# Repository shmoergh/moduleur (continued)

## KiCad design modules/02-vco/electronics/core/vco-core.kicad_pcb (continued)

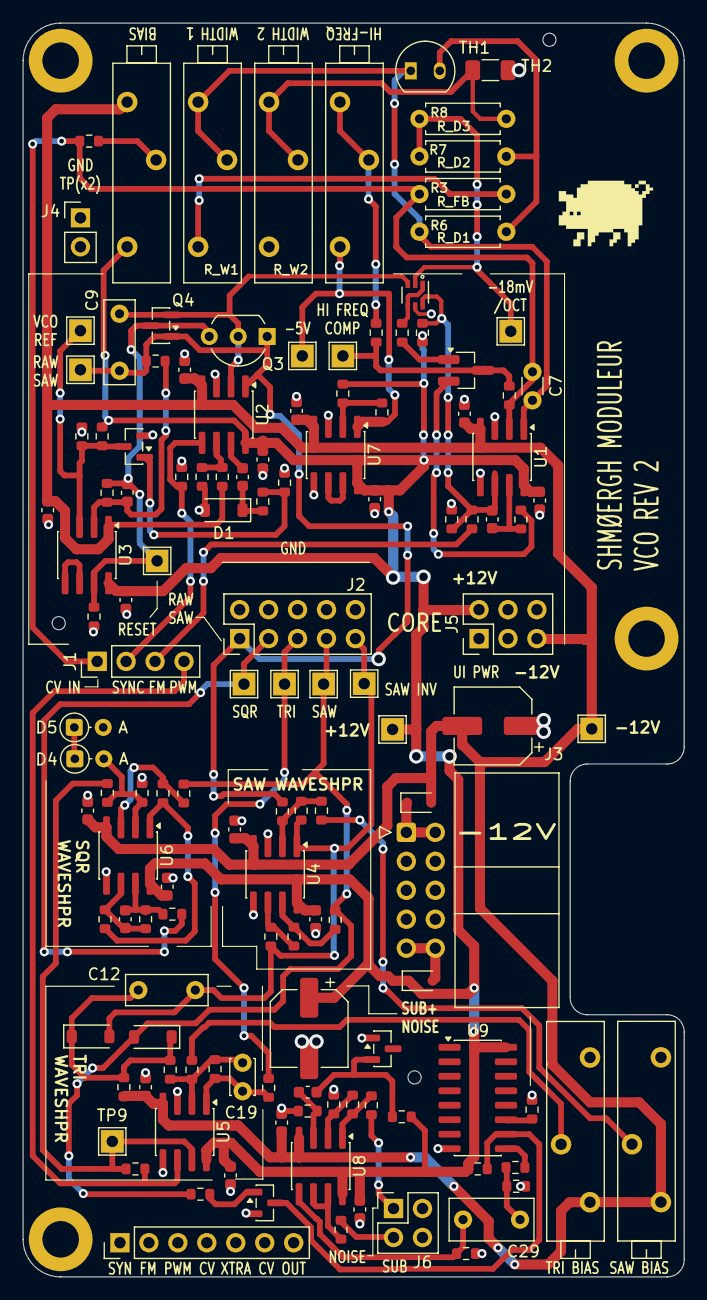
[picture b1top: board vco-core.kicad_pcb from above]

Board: 2 copper layers, 58.0 x 110.0 mm, 138 parts (0 on the bottom side), 67 nets.

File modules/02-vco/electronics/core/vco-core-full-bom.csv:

"Reference","Value","Qty","Exclude from BOM","Footprint","LCSC","Mouser Part no.","Part URL","Vendor","CHECKED"
"C1,C2,C3,C4,C5,C6,C13,C14,C15,C16,C17,C18,C21,C22,C26,C27","100n","16","","Capacitor_SMD:C_0603_1608Metric","C14663","","","JLCPCB","YES"
"C8","100p","1","","Capacitor_SMD:C_0603_1608Metric","C14858","","","JLCPCB","YES"
"C9","2.2nF (foil)","1","","Capacitor_THT:C_Rect_L7.2mm_W2.5mm_P5.00mm_FKS2_FKP2_MKS2_MKP2","","80-R82MC1220AA50J ","https://mou.sr/4eLPHe3","Mouser","YES"
"C10","22p","1","","Capacitor_SMD:C_0603_1608Metric","C1653","","","JLCPCB","YES"
"C11","47p","1","","Capacitor_SMD:C_0603_1608Metric","C1671","","","JLCPCB","YES"
"C20","33p","1","","Capacitor_SMD:C_0603_1608Metric","C1663","","","JLCPCB","YES"
"C23,C24","100u","2","","Capacitor_SMD:CP_Elec_6.3x7.7","C2836442","","","JLCPCB","YES"
"C28","1u","1","","Capacitor_SMD:C_0603_1608Metric","C15849","","","JLCPCB","YES"
"C29","470n","1","","Capacitor_THT:C_Rect_L7.2mm_W3.5mm_P5.00mm_FKS2_FKP2_MKS2_MKP2","","80-R82DC3470DQ60K","https://mou.sr/4lPhH2D","Mouser","YES"
"D1,D2,D3","1N4148","3","","Diode_SMD:D_SOD-123","C81598","","","JLCPCB","YES"
"D6,D7","1N5817","2","","Diode_SMD:D_SOD-323","C5190152","","","JLCPCB","YES"
"J1","Conn_01x04","1","","Connector_PinHeader_2.54mm:PinHeader_1x04_P2.54mm_Vertical","","200-HTSW10407TS","https://mou.sr/3UfnMcJ","Mouser","YES"
"J2","Conn_02x05_Odd_Even","1","","Connector_PinHeader_2.54mm:PinHeader_2x05_P2.54mm_Vertical","","200-TSW10507TD","https://mou.sr/40QhDaC","Mouser","YES"
"J3","Conn_02x05_Odd_Even","1","","Connector_IDC:IDC-Header_2x05_P2.54mm_Horizontal","","571-5103310-1","https://mou.sr/3GwYxj9","Mouser","YES"
"J4","Conn_01x02","1","","Connector_PinHeader_2.54mm:PinHeader_1x02_P2.54mm_Vertical","","200-HTSW10207TS","https://mou.sr/3IruU3e","Mouser","YES"
"J5","Conn_02x03_Odd_Even","1","","Connector_PinHeader_2.54mm:PinHeader_2x03_P2.54mm_Vertical","","200-TSW10307TD","https://mou.sr/4liCQlU","Mouser","YES"
"J6","Conn_02x02_Counter_Clockwise","1","","Connector_PinHeader_2.54mm:PinHeader_2x02_P2.54mm_Vertical","","200-HTSW10207TD","https://mou.sr/3TDBcz9","Mouser","YES"
"J8","Conn_01x07","1","","Connector_PinHeader_2.54mm:PinHeader_1x07_P2.54mm_Vertical","","474-PRT-09280","","Mouser",""
"Q1","BC847BS","1","","Package_TO_SOT_SMD:SOT-363_SC-70-6","C5380687","","","JLCPCB","YES"
"Q2","MMBT3906","1","","Package_TO_SOT_SMD:SOT-23_Handsoldering","C7420354","","","JLCPCB","YES"
"Q3","J111","1","","Package_TO_SOT_THT:TO-92_Inline_Wide","","512-J111","https://mou.sr/4f5W0HS","Mouser","YES"
"Q4","MMBFJ111","1","","Package_TO_SOT_SMD:SOT-23","C274688","","","JLCPCB","YES"
"Q5,Q7","MMBT5551","2","","Package_TO_SOT_SMD:SOT-23","C2145","","","JLCPCB","YES"
"Q6","BC847","1","","Package_TO_SOT_SMD:SOT-23","C8664","","","JLCPCB","YES"
"R1,R5,R15,R18,R21,R25,R27,R28,R29,R30,R37,R38,R40,R41,R43,R57","100k","16","","Resistor_SMD:R_0603_1608Metric","C25803","","","JLCPCB","YES"
"R2,R17","150k","2","","Resistor_SMD:R_0603_1608Metric","C22807","","","JLCPCB","YES"
"R3,R6,R7,R8","See t.comp. table","4","","Shmoergh_Custom_Footprints:R_Axial_DIN0207_L6.3mm_D2.5mm_P7.62mm_Horizontal","","","https://hu.mouser.com/ProductDetail/YAGEO/MFR50SFTE52-4R22?q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","",""
"R4,R10,R13","1M","3","","Resistor_SMD:R_0603_1608Metric","C22935","","","JLCPCB","YES"
"R9,R11","1.5k","2","","Resistor_SMD:R_0603_1608Metric","C22843","","","JLCPCB","YES"
"R12","510","1","","Resistor_SMD:R_0603_1608Metric","C23193","","","JLCPCB","YES"
"R14,R47","10k","2","","Resistor_SMD:R_0603_1608Metric","C25804","","","JLCPCB","YES"
"R16","22k","1","","Resistor_SMD:R_0603_1608Metric","C31850","","","JLCPCB","YES"
"R19","330k","1","","Resistor_SMD:R_0603_1608Metric","C23137","","","JLCPCB","YES"
"R20,R33","2.2k","2","","Resistor_SMD:R_0603_1608Metric","C4190","","","JLCPCB","YES"
"R22,R32,R45,R46","47k","4","","Resistor_SMD:R_0603_1608Metric","C25819","","","JLCPCB","YES"
"R23,R24","15k","2","","Resistor_SMD:R_0603_1608Metric","C22809","","","JLCPCB","YES"
"R26","27k","1","","Resistor_SMD:R_0603_1608Metric","C22967","","","JLCPCB","YES"
"R31,R34,R44,R56","220k","4","","Resistor_SMD:R_0603_1608Metric","C22961","","","JLCPCB","YES"
"R35","2.2M","1","","Resistor_SMD:R_0603_1608Metric","C22938","","","JLCPCB","YES"
"R36,R39","240k","2","","Resistor_SMD:R_0603_1608Metric","C4197","","","JLCPCB","YES"
"R42","680","1","","Resistor_SMD:R_0603_1608Metric","C23228","","","JLCPCB","YES"
"R48","56k","1","","Resistor_SMD:R_0603_1608Metric","C23206","","","JLCPCB","YES"
"R50,R52,R53,R54,R55","1k","5","","Resistor_SMD:R_0603_1608Metric","C21190","","","JLCPCB","YES"
"RV_SAW_BIAS1","10k (prec)","1","","Potentiometer_THT:Potentiometer_Bourns_3006P_Horizontal","","652-3006P-1-103-LF ","https://mou.sr/41xh2vW","Mouser","YES"
"RV_TRI_BIAS1,R_BIAS1","100k (prec)","2","","Potentiometer_THT:Potentiometer_Bourns_3006P_Horizontal","","652-3006P-1-104-LF","https://mou.sr/4ff5W1E","Mouser","YES"
"R_HIFREQ1","2k (prec)","1","","Potentiometer_THT:Potentiometer_Bourns_3006P_Horizontal","","652-3006P-1-202-LF","https://mou.sr/3ZK9AMt","Mouser","YES"
"R_WIDTH1,R_WIDTH2","See t.comp. table","2","","Potentiometer_THT:Potentiometer_Bourns_3006P_Horizontal","","652-3006P-1-501-LF,652-3006P-7-203-LF","https://mou.sr/3GyUiUc,https://mou.sr/41re1x3","Mouser",""
"TH1","See t.comp. table","1","","Package_TO_SOT_THT:TO-92-2","","594-2381-640-55103","https://mou.sr/4nM5nSy","Mouser","YES"
"TH2","PTS120602B100RP100","1","","Resistor_SMD:R_1206_3216Metric_Pad1.30x1.75mm_HandSolder","","594-PTS120601B100RP","https://hu.mouser.com/ProductDetail/594-PTS120601B100RP","Mouser","YES"
"U1,U2,U4,U5,U6,U7,U8","TL072","7","","Package_SO:SOIC-8_3.9x4.9mm_P1.27mm","C6961","","","JLCPCB","YES"
"U3","LM311","1","","Package_SO:SOIC-8_3.9x4.9mm_P1.27mm","C12597","","","JLCPCB","YES"
"U9","CD4040BM96","1","","Package_SO:SOIC-16_3.9x9.9mm_P1.27mm","C353974","","","JLCPCB","YES"
"C7","100p-1n","1","Excluded from BOM","Capacitor_THT:C_Disc_D3.0mm_W1.6mm_P2.50mm","","","","","YES"
"C12","10p-100p","1","Excluded from BOM","Capacitor_THT:C_Rect_L7.0mm_W2.5mm_P5.00mm","","","","","YES"
"C19","22p","1","Excluded from BOM","Capacitor_THT:C_Disc_D3.0mm_W2.0mm_P2.50mm","","","","","YES"
"D4,D5","5.1V","2","Excluded from BOM","Diode_THT:D_DO-34_SOD68_P2.54mm_Vertical_AnodeUp","","","","","YES"
"H1,H2,H3,H4","MountingHole","4","Excluded from BOM","MountingHole:MountingHole_3.2mm_M3_DIN965_Pad","","","","","YES"
"TP1","-18mV/V","1","Excluded from BOM","TestPoint:TestPoint_THTPad_2.0x2.0mm_Drill1.0mm","","","","","YES"
"TP2","HiFreq","1","Excluded from BOM","TestPoint:TestPoint_THTPad_2.0x2.0mm_Drill1.0mm","","","","","YES"
"TP3","RAW_SAW","1","Excluded from BOM","TestPoint:TestPoint_THTPad_2.0x2.0mm_Drill1.0mm","","","","","YES"
"TP4","VCOVREF","1","Excluded from BOM","TestPoint:TestPoint_THTPad_2.0x2.0mm_Drill1.0mm","","","","","YES"
"TP5","Reset OUT","1","Excluded from BOM","TestPoint:TestPoint_THTPad_2.0x2.0mm_Drill1.0mm","","","","","YES"
"TP6","SAWInv","1","Excluded from BOM","TestPoint:TestPoint_THTPad_2.0x2.0mm_Drill1.0mm","","","","","YES"
"TP7","SAW","1","Excluded from BOM","TestPoint:TestPoint_THTPad_2.0x2.0mm_Drill1.0mm","","","","","YES"
"TP8","TRI","1","Excluded from BOM","TestPoint:TestPoint_THTPad_2.0x2.0mm_Drill1.0mm","","","","","YES"
"TP9","PW","1","Excluded from BOM","TestPoint:TestPoint_THTPad_2.0x2.0mm_Drill1.0mm","","","","","YES"
"TP10","SQR","1","Excluded from BOM","TestPoint:TestPoint_THTPad_2.0x2.0mm_Drill1.0mm","","","","","YES"
"TP11","-5V","1","Excluded from BOM","TestPoint:TestPoint_THTPad_2.0x2.0mm_Drill1.0mm","","","","","YES"
"TP12","12V","1","Excluded from BOM","TestPoint:TestPoint_THTPad_2.0x2.0mm_Drill1.0mm","","","","","YES"
"TP13","-12V","1","Excluded from BOM","TestPoint:TestPoint_THTPad_2.0x2.0mm_Drill1.0mm","","","","","YES"

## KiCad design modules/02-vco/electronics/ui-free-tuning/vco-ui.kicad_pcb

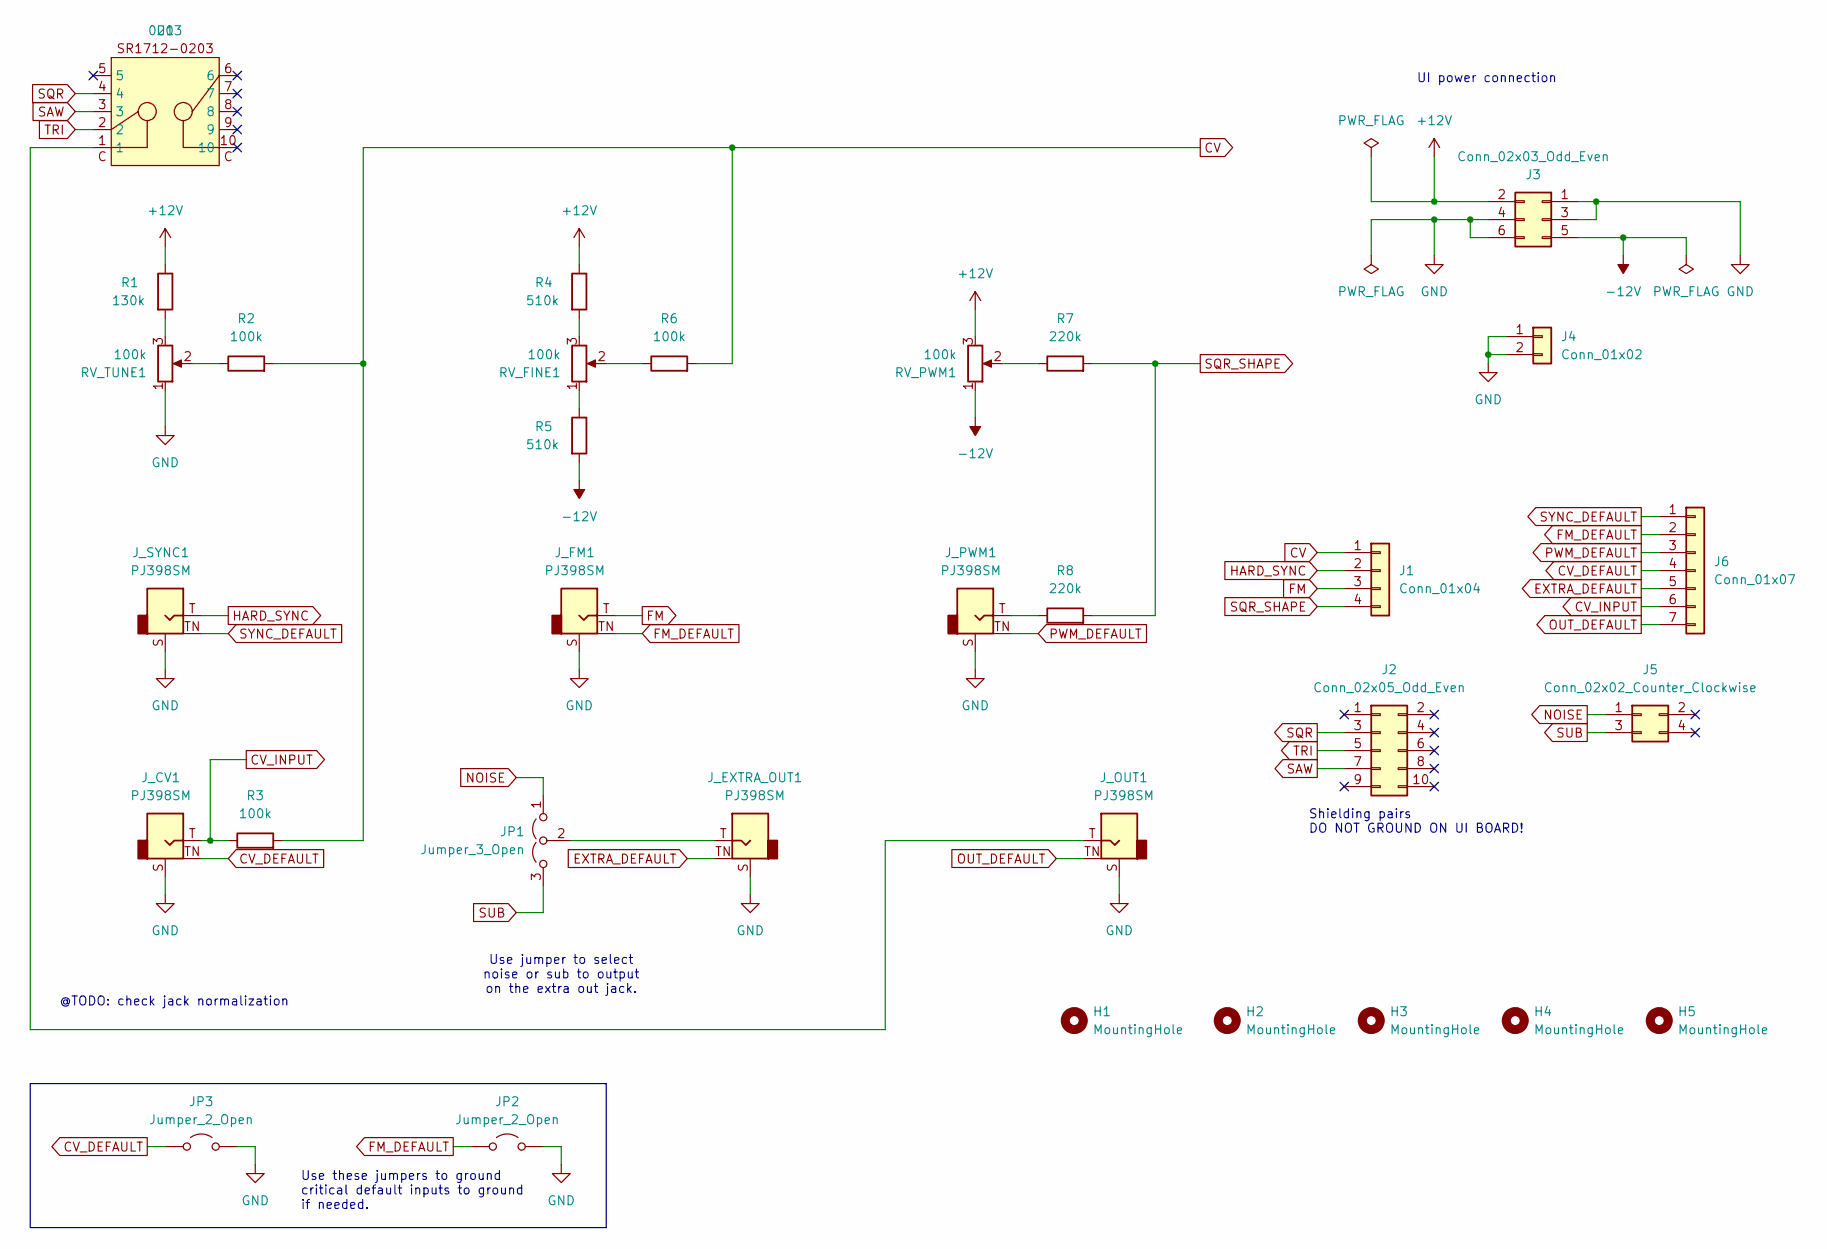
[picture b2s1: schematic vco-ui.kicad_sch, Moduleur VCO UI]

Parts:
H1, H2, H3, H4, H5: MountingHole; MountingHole_3.2mm_M3_DIN965_Pad
J1: Conn_01x04; PinSocket_1x04_P2.54mm_Vertical; Part no. 200-SSW10401TMS
J2: Conn_02x05_Odd_Even; PinSocket_2x05_P2.54mm_Vertical; Part no. 200-SSW10501TD
J3: Conn_02x03_Odd_Even; PinSocket_2x03_P2.54mm_Vertical; Part no. 200-SSW10301TD
J4: Conn_01x02; PinSocket_1x02_P2.54mm_Vertical; Part no. 200-SSW10201TS
J5: Conn_02x02_Counter_Clockwise; PinSocket_2x02_P2.54mm_Vertical; Part no. 200-SSW10206TD
J6: Conn_01x07; PinSocket_1x07_P2.54mm_Vertical; Part no. 200-SSW10601TS
JP1: Jumper_3_Open; PinHeader_1x03_P2.54mm_Horizontal; Part no. 200-HTSW10308TSRA
JP2, JP3: Jumper_2_Open; PinHeader_1x02_P2.54mm_Horizontal; Part no. 200-HTSW10208TSRA
J_CV1: PJ398SM; Jack_3.5mm_QingPu_WQP-PJ398SM_Vertical_CircularHoles; Part no. PJ398SM
J_EXTRA_OUT1: PJ398SM; Jack_3.5mm_QingPu_WQP-PJ398SM_Vertical_CircularHoles; Part no. PJ398SM
J_FM1: PJ398SM; Jack_3.5mm_QingPu_WQP-PJ398SM_Vertical_CircularHoles; Part no. PJ398SM
J_OUT1: PJ398SM; Jack_3.5mm_QingPu_WQP-PJ398SM_Vertical_CircularHoles; Part no. PJ398SM
J_PWM1: PJ398SM; Jack_3.5mm_QingPu_WQP-PJ398SM_Vertical_CircularHoles; Part no. PJ398SM
J_SYNC1: PJ398SM; Jack_3.5mm_QingPu_WQP-PJ398SM_Vertical_CircularHoles; Part no. PJ398SM
R1: 130k; R_Axial_DIN0207_L6.3mm_D2.5mm_P7.62mm_Horizontal; Part no. 603-MFR-25FBF52-130K
R2, R3, R6: 100k; R_Axial_DIN0207_L6.3mm_D2.5mm_P7.62mm_Horizontal; Part no. 603-MFR-25FRF52100K
R4, R5: 510k; R_Axial_DIN0207_L6.3mm_D2.5mm_P7.62mm_Horizontal; Part no. 603-MFR-25FBF52-510K
R7, R8: 220k; R_Axial_DIN0207_L6.3mm_D2.5mm_P7.62mm_Horizontal; Part no. 603-MFR-25FRF52-220K
RV_FINE1: 100k; Potentiometer_Bourns_Single-PTV09A; Part no. 652-PTV09A4025UB104
RV_PWM1: 100k; Potentiometer_Bourns_Single-PTV09A; Part no. 652-PTV09A4025UB104
RV_TUNE1: 100k; Potentiometer_Bourns_Single-PTV09A; Part no. 652-PTV09A4025UB104
U1: 0203; SR1712-0203; Part no. 105-SR1712F-23NS

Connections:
+12V: J3.2, R1.1, R4.1, RV_PWM1.3
-12V: J3.5, R5.2, RV_PWM1.1
CV: J1.1, R2.2, R3.2, R6.2
CV_DEFAULT: J6.4, JP3.1 (A), J_CV1.TN
CV_INPUT: J6.6, J_CV1.T, R3.1
EXTRA_DEFAULT: J6.5, J_EXTRA_OUT1.TN
FM: J1.3, J_FM1.T
FM_DEFAULT: J6.2, JP2.1 (A), J_FM1.TN
GND: J3.1, J3.3, J3.4, J3.6, J4.1, J4.2, JP2.2 (B), JP3.2 (B), J_CV1.S, J_EXTRA_OUT1.S, J_FM1.S, J_OUT1.S, J_PWM1.S, J_SYNC1.S, RV_TUNE1.1
HARD_SYNC: J1.2, J_SYNC1.T
NOISE: J5.1, JP1.1 (A)
unnamed: JP1.2 (C), J_EXTRA_OUT1.T
unnamed: J_OUT1.T, U1.1
unnamed: J_PWM1.T, R8.1
unnamed: R1.2, RV_TUNE1.3
unnamed: R2.1, RV_TUNE1.2
unnamed: R4.2, RV_FINE1.3
unnamed: R5.1, RV_FINE1.1
unnamed: R6.1, RV_FINE1.2
unnamed: R7.1, RV_PWM1.2
OUT_DEFAULT: J6.7, J_OUT1.TN
PWM_DEFAULT: J6.3, J_PWM1.TN
SAW: J2.7, U1.3
SQR: J2.3, U1.4
SQR_SHAPE: J1.4, R7.2, R8.2
SUB: J5.3, JP1.3 (B)
SYNC_DEFAULT: J6.1, J_SYNC1.TN
TRI: J2.5, U1.2

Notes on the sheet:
@TODO: check jack normalization
Use these jumpers to ground critical default inputs to ground if needed.
UI power connection
Use jumper to select noise or sub to output on the extra out jack.
Shielding pairs DO NOT GROUND ON UI BOARD!

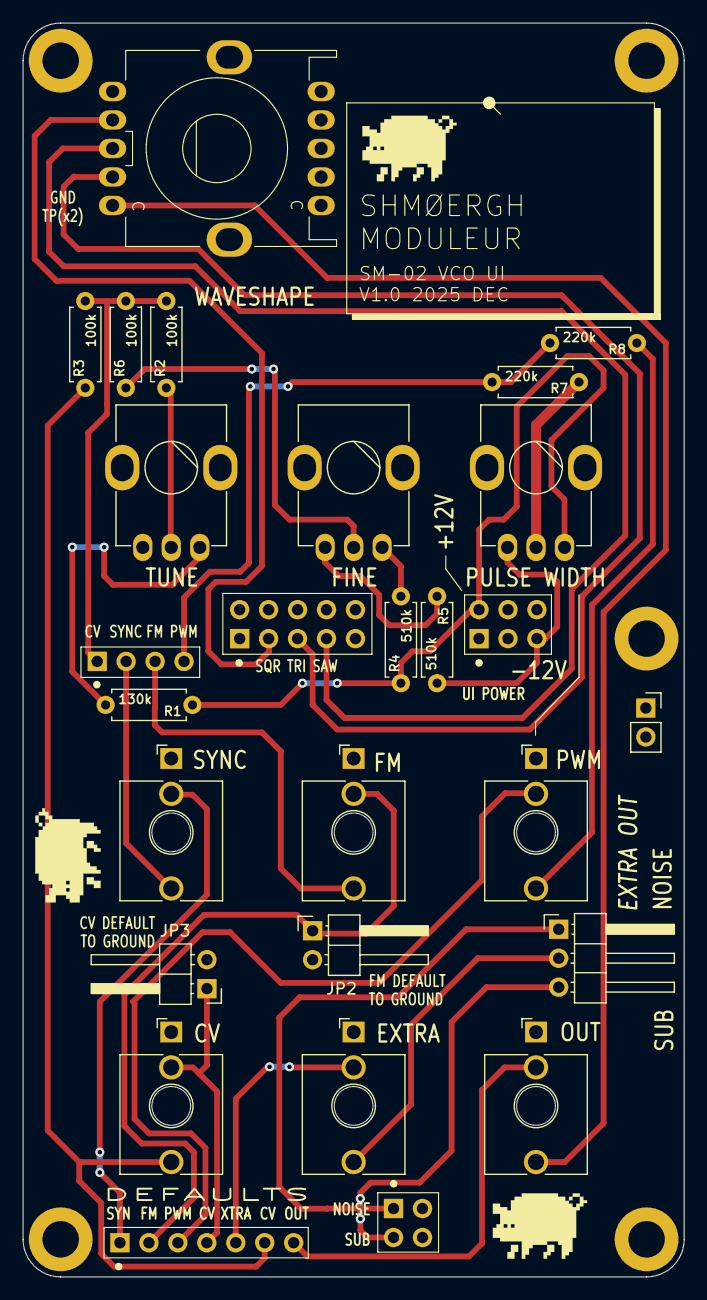
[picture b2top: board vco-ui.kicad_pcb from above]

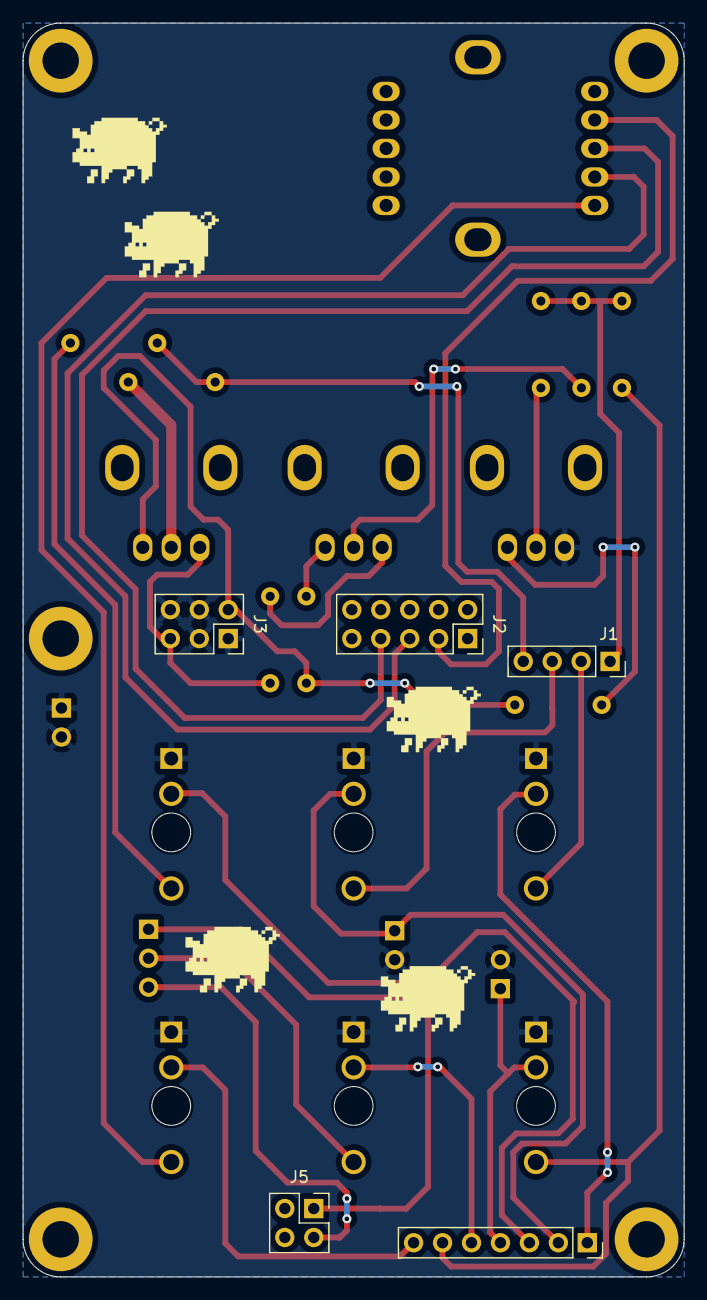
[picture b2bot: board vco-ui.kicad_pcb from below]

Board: 2 copper layers, 58.0 x 110.0 mm, 32 parts (5 on the bottom side), 28 nets.

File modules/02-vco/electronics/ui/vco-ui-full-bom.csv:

"Reference","Qty","Value","DNP","Exclude from BOM","Exclude from Board","Footprint","Datasheet","Part no.","Part URL","Vendor","Note"
"J1","1","Conn_01x04","","","","Connector_PinSocket_2.54mm:PinSocket_1x04_P2.54mm_Vertical","~","200-SSW10401TMS","https://mou.sr/4kxE3Vr","Mouser",""
"J2","1","Conn_02x05_Odd_Even","","","","Connector_PinSocket_2.54mm:PinSocket_2x05_P2.54mm_Vertical","~","200-SSW10501TD","https://mou.sr/4lVCZM9","Mouser",""
"J3","1","Conn_02x03_Odd_Even","","","","Connector_PinSocket_2.54mm:PinSocket_2x03_P2.54mm_Vertical","~","200-SSW10301TD","https://mou.sr/3GIDVEr","Mouser",""
"J4","1","Conn_01x02","","","","Connector_PinSocket_2.54mm:PinSocket_1x02_P2.54mm_Vertical","~","200-SSW10201TS","https://mou.sr/4lBvdHe","Mouser",""
"J5","1","Conn_02x02_Counter_Clockwise","","","","Connector_PinSocket_2.54mm:PinSocket_2x02_P2.54mm_Vertical","~","200-SSW10206TD","https://mou.sr/4eSbYqI","Mouser",""
"J6","1","Conn_01x07","","","","Connector_PinSocket_2.54mm:PinSocket_1x07_P2.54mm_Vertical","~","200-SSW10601TS","https://mou.sr/4lnf48h","Mouser",""
"JP1","1","Jumper_3_Open","","","","Connector_PinHeader_2.54mm:PinHeader_1x03_P2.54mm_Horizontal","~","200-HTSW10308TSRA","https://mou.sr/451l2py","Mouser",""
"JP2,JP3","2","Jumper_2_Open","","","","Connector_PinHeader_2.54mm:PinHeader_1x02_P2.54mm_Horizontal","~","200-HTSW10208TSRA","https://mou.sr/4nM6IZz","Mouser",""
"J_CV1,J_EXTRA_OUT1,J_FM1,J_OUT1,J_PWM1,J_SYNC1","6","PJ398SM","","","","Shmoergh_Custom_Footprints:Jack_3.5mm_QingPu_WQP-PJ398SM_Vertical_CircularHoles","~","PJ398SM","https://www.thonk.co.uk/shop/thonkiconn/","Thonk",""
"R1","1","130k","","","","Shmoergh_Custom_Footprints:R_Axial_DIN0207_L6.3mm_D2.5mm_P7.62mm_Horizontal","~","603-MFR-25FBF52-130K ","https://mou.sr/3XNtowV","Mouser",""
"R2,R3,R6","3","100k","","","","Shmoergh_Custom_Footprints:R_Axial_DIN0207_L6.3mm_D2.5mm_P7.62mm_Horizontal","~","603-MFR-25FRF52100K","https://mou.sr/4hEwI4G","Mouser",""
"R4,R5","2","510k","","","","Shmoergh_Custom_Footprints:R_Axial_DIN0207_L6.3mm_D2.5mm_P7.62mm_Horizontal","~","603-MFR-25FBF52-510K ","https://mou.sr/44Vd3Kk","Mouser",""
"R7,R8","2","220k","","","","Shmoergh_Custom_Footprints:R_Axial_DIN0207_L6.3mm_D2.5mm_P7.62mm_Horizontal","~","603-MFR-25FRF52-220K","https://mou.sr/46cEvF7","Mouser",""
"RV_FINE1,RV_PWM1,RV_TUNE1","3","100k","","","","Shmoergh_Custom_Footprints:Potentiometer_Bourns_Single-PTV09A","~","652-PTV09A4025UB104","https://mou.sr/41lYe2k","Mouser","Knurled Shaft"
"U1","1","0203","","","","Shmoergh_Custom_Footprints:SR1712-0203","https://hu.mouser.com/datasheet/2/13/SR1712F-1815245.pdf","105-SR1712F-23NS","https://mou.sr/3U6bGTk","Mouser",""

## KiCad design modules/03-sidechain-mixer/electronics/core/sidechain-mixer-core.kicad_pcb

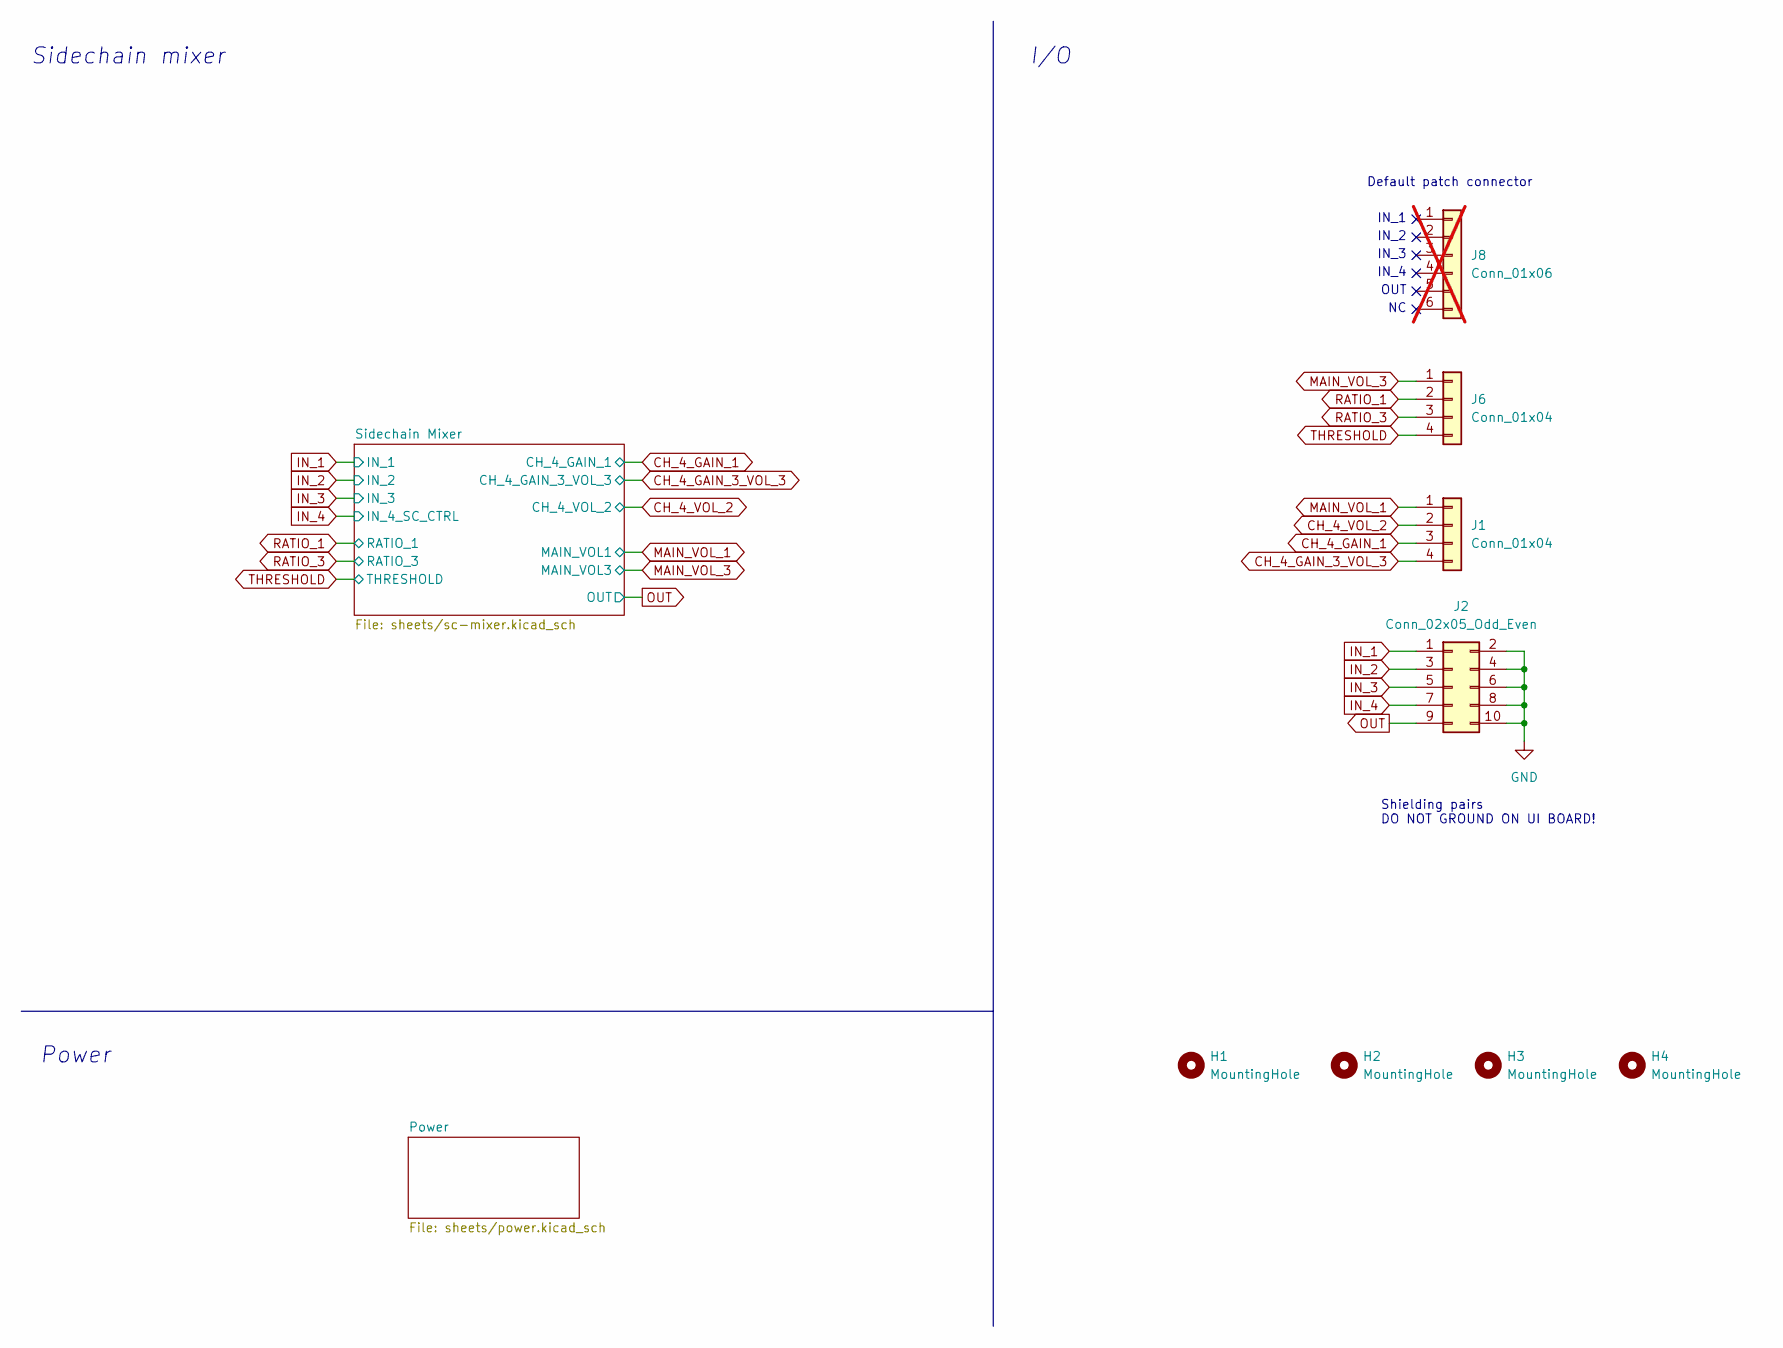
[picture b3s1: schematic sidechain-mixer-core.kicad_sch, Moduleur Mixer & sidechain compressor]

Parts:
H1, H2, H3, H4: MountingHole; MountingHole_3.2mm_M3_DIN965_Pad
J1, J6: Conn_01x04; PinHeader_1x04_P2.54mm_Vertical; Mouser Part no. 200-HTSW10407TS
J2: Conn_02x05_Odd_Even; PinHeader_2x05_P2.54mm_Vertical; Mouser Part no. 200-HTSW10507TD
J8: Conn_01x06; PinHeader_1x06_P2.54mm_Vertical; Mouser Part no. 200-HTSW10607TS; not fitted

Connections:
CH_4_GAIN_1: J1.3; also elsewhere on the board
CH_4_GAIN_3_VOL_3: J1.4; also elsewhere on the board
CH_4_VOL_2: J1.2; also elsewhere on the board
IN_1: J2.1; also elsewhere on the board
IN_2: J2.3; also elsewhere on the board
IN_3: J2.5; also elsewhere on the board
IN_4: J2.7; also elsewhere on the board
MAIN_VOL_1: J1.1; also elsewhere on the board
MAIN_VOL_3: J6.1; also elsewhere on the board
OUT: J2.9; also elsewhere on the board
RATIO_1: J6.2; also elsewhere on the board
RATIO_3: J6.3; also elsewhere on the board
THRESHOLD: J6.4; also elsewhere on the board

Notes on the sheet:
Power
IN_3
Default patch connector
IN_1
Shielding pairs DO NOT GROUND ON UI BOARD!
OUT
Sidechain mixer
IN_2
I/O
IN_4

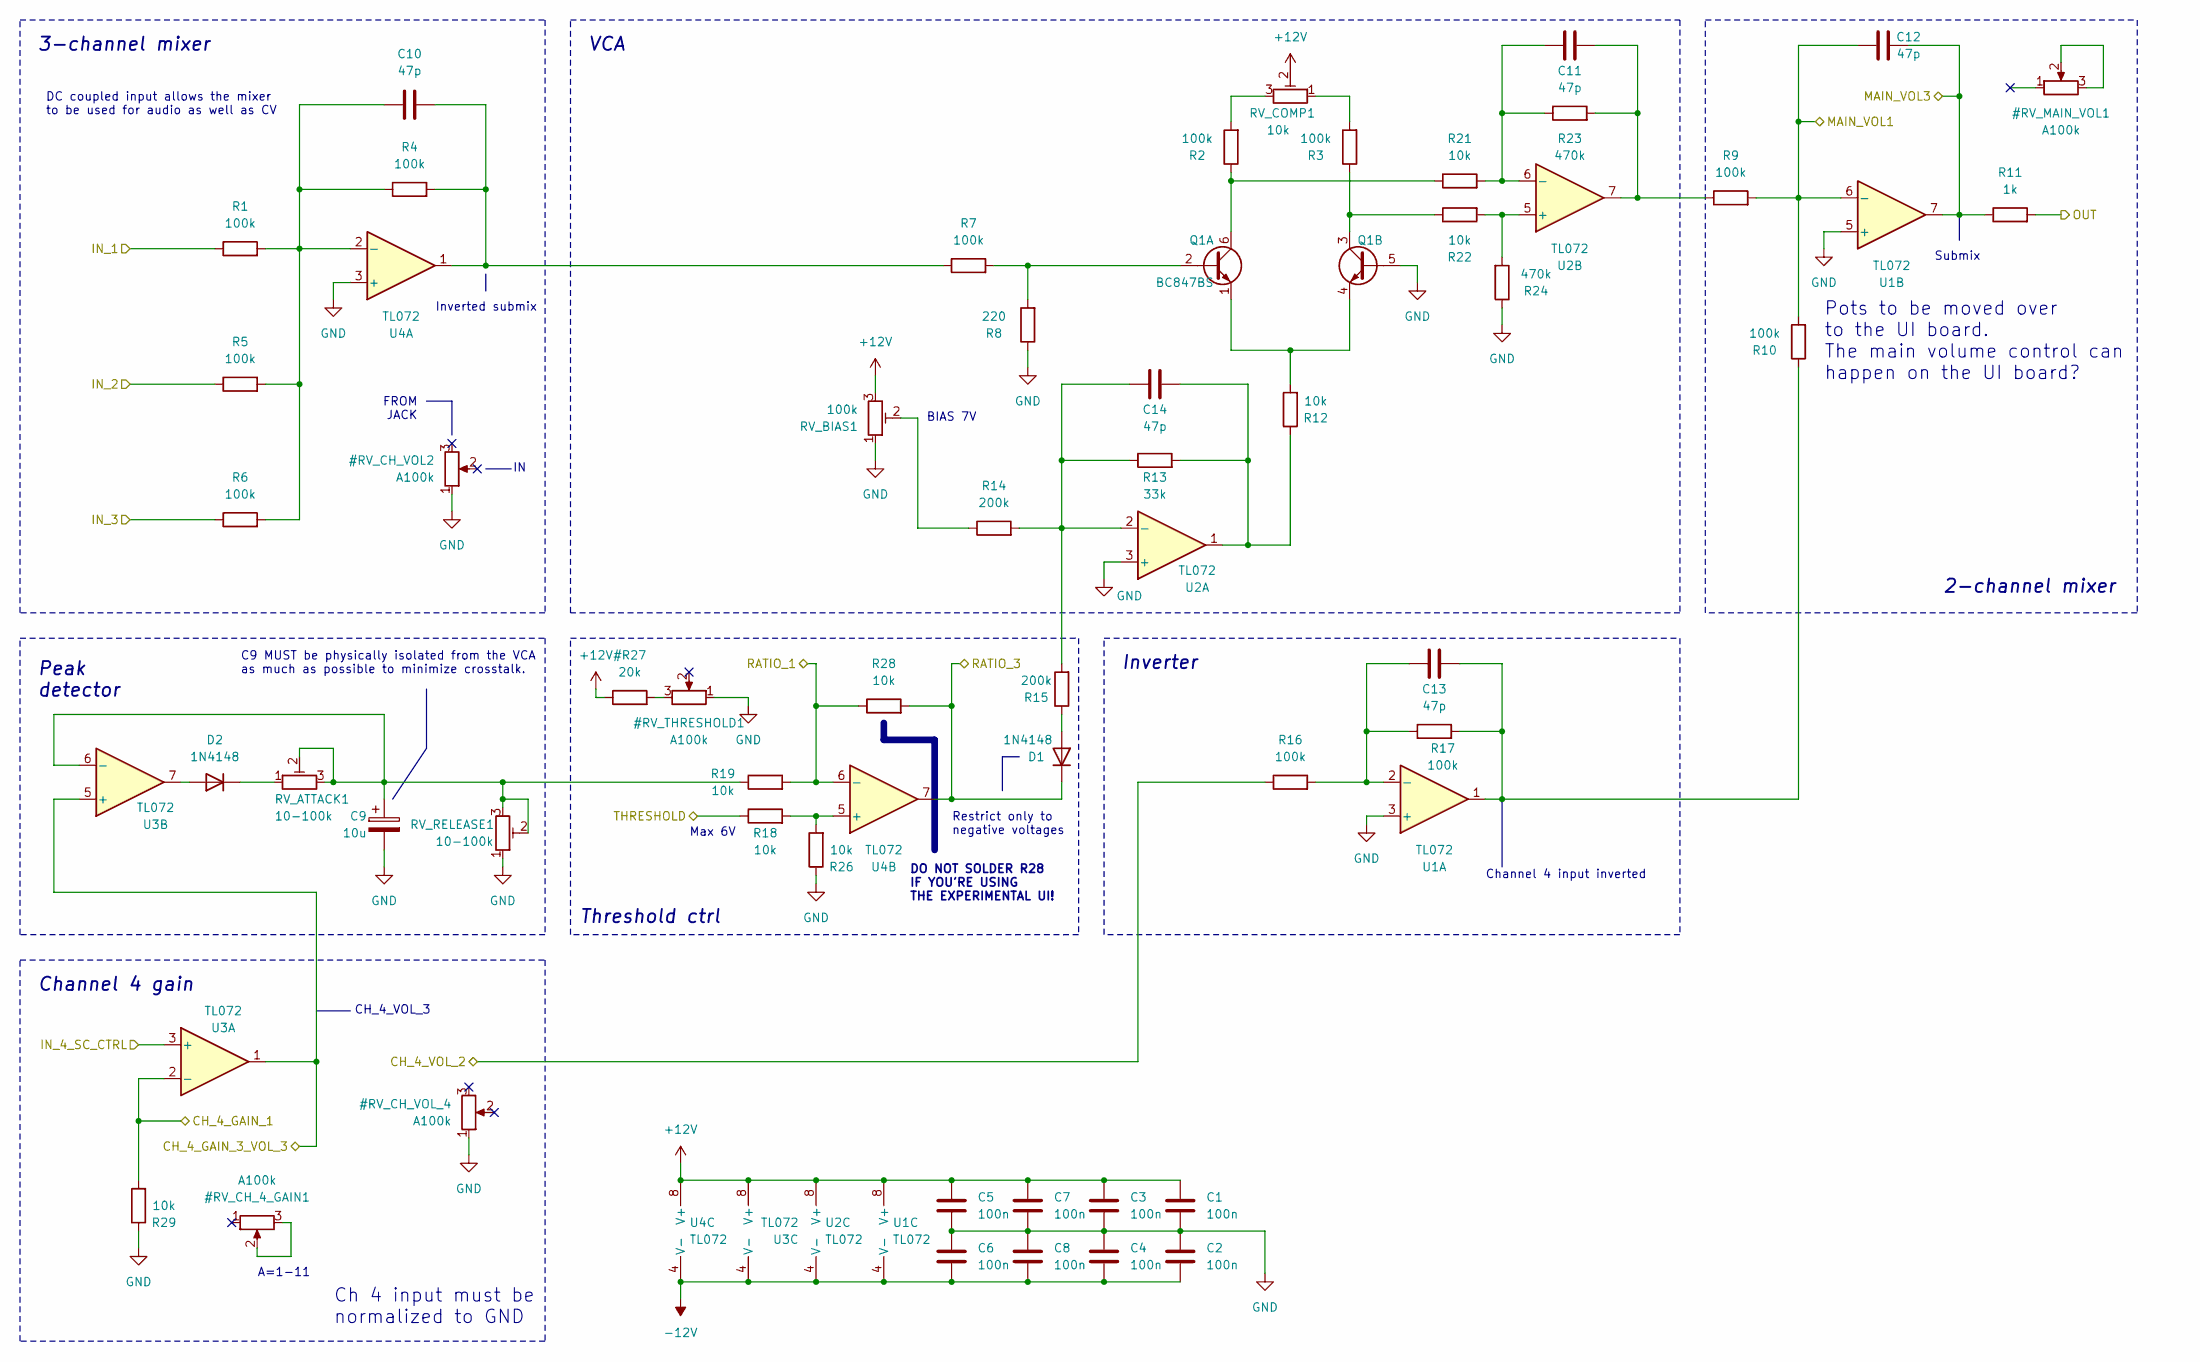
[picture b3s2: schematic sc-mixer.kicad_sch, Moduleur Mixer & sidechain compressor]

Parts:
C1, C2, C3, C4, C5, C6, C7, C8: 100n; C_0603_1608Metric; LCSC C14663
C9: 10u; CP_Elec_5x5.4; LCSC C30110
C10, C11, C12, C13, C14: 47p; C_0603_1608Metric_Pad1.08x0.95mm_HandSolder; LCSC C1671
D1, D2: 1N4148; D_SOD-123; LCSC C81598
Q1: BC847BS; SOT-363_SC-70-6; LCSC C5380687
R1, R2, R3, R4, R5, R6, R7, R9, R10, R16, R17: 100k; R_0603_1608Metric; LCSC C25803
R8: 220; R_0603_1608Metric; LCSC C22962
R11: 1k; R_0603_1608Metric; LCSC C21190
R12, R21, R22: 10k; R_0603_1608Metric; LCSC C25804
R13: 33k; R_0603_1608Metric; LCSC C4216
R14, R15: 200k; R_0603_1608Metric; LCSC C25811
R18, R19, R26, R28, R29: 10k; R_Axial_DIN0207_L6.3mm_D2.5mm_P7.62mm_Horizontal; Mouser Part no. 603-MFR-25FRF5210K
R23, R24: 470k; R_0603_1608Metric; LCSC C23178
RV_ATTACK1: 10-100k; Potentiometer_ACP_CA6-H2,5_Horizontal; Mouser Part no. 774-06TR4AA103CP
RV_BIAS1: 100k; Potentiometer_ACP_CA6-H2,5_Horizontal; Mouser Part no. 774-06TR4AA104CP
RV_COMP1: 10k; Potentiometer_ACP_CA6-H2,5_Horizontal; Mouser Part no. 774-06TR4AA103CP
RV_RELEASE1: 10-100k; Potentiometer_ACP_CA6-H2,5_Horizontal; Mouser Part no. 774-06TR4AA103CP
U1, U2, U3, U4: TL072; SOIC-8_3.9x4.9mm_P1.27mm; LCSC C6961

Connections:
-12V: C2.2, C4.2, C6.2, C8.2, U1.4 (V-), U2.4 (V-), U3.4 (V-), U4.4 (V-); also elsewhere on the board
CH_4_GAIN_1: R29.2, U3.2 (-); also elsewhere on the board
CH_4_GAIN_3_VOL_3: U3.1, U3.5 (+); also elsewhere on the board
CH_4_VOL_2: R16.1; also elsewhere on the board
IN_1: R1.1; also elsewhere on the board
IN_2: R5.1; also elsewhere on the board
IN_3: R6.1; also elsewhere on the board
IN_4: U3.3 (+); also elsewhere on the board
MAIN_VOL_1: C12.1, R9.2, R10.2, U1.6 (-); also elsewhere on the board
MAIN_VOL_3: C12.2, R11.1, U1.7; also elsewhere on the board
unnamed: C10.2, R4.2, R7.1, U4.1
unnamed: C11.2, R9.1, R23.2, U2.7
unnamed: C13.2, R10.1, R17.2, U1.1
unnamed: C14.2, R12.1, R13.2, U2.1
unnamed: D1.2 (A), R15.1
unnamed: D2.2 (A), U3.7
unnamed: D2.1 (K), RV_ATTACK1.1
unnamed: Q1.2 (B1), R7.2, R8.2
unnamed: Q1.6 (C1), R2.1, R21.1
unnamed: Q1.1 (E1), Q1.4 (E2), R12.2
unnamed: Q1.3 (C2), R3.1, R22.1
unnamed: R2.2, RV_COMP1.3
unnamed: R3.2, RV_COMP1.1
unnamed: R14.1, RV_BIAS1.2
unnamed: C13.1, R16.2, R17.1, U1.2 (-)
unnamed: C14.1, R13.1, R14.2, R15.2, U2.2 (-)
unnamed: R22.2, R24.2, U2.5 (+)
unnamed: C11.1, R21.2, R23.1, U2.6 (-)
unnamed: C9.1, R19.1, RV_ATTACK1.2, RV_ATTACK1.3, RV_RELEASE1.2, RV_RELEASE1.3, U3.6 (-)
unnamed: C10.1, R1.2, R4.1, R5.2, R6.2, U4.2 (-)
unnamed: R18.2, R26.2, U4.5 (+)
OUT: R11.2; also elsewhere on the board
RATIO_1: R19.2, R28.1, U4.6 (-); also elsewhere on the board
RATIO_3: D1.1 (K), R28.2, U4.7; also elsewhere on the board
THRESHOLD: R18.1; also elsewhere on the board

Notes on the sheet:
2-channel mixer
Channel 4 gain
FROM JACK
A=1-11
Pots to be moved over to the UI board. The main volume control can happen on the UI board?
DO NOT SOLDER R28 IF YOU'RE USING THE EXPERIMENTAL UI!
Inverter
Submix
VCA
BIAS 7V
Channel 4 input inverted
Max 6V
Ch 4 input must be normalized to GND
3-channel mixer
Restrict only to negative voltages
DC coupled input allows the mixer to be used for audio as well as CV
C9 MUST be physically isolated from the VCA as much as possible to minimize crosstalk.
CH_4_VOL_3
Peak detector
Threshold ctrl
Inverted submix

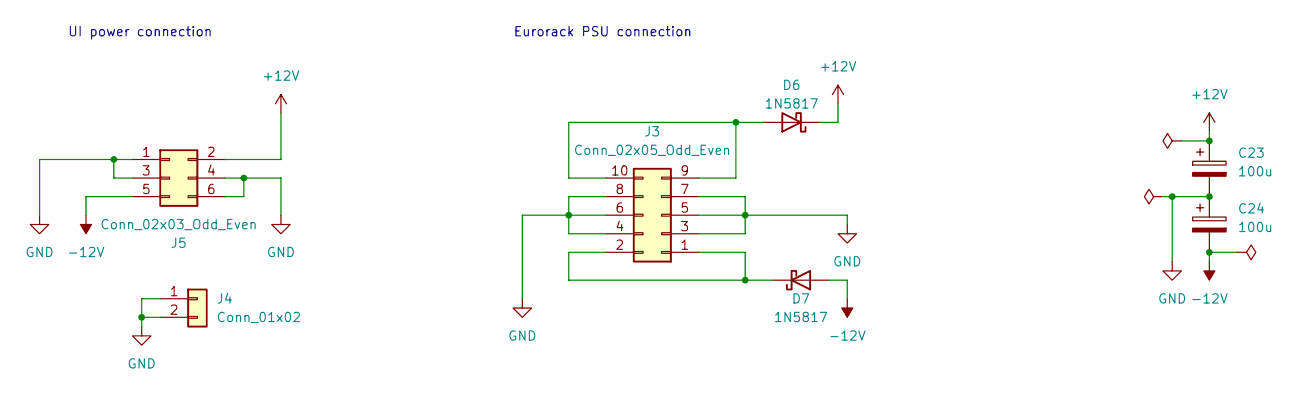
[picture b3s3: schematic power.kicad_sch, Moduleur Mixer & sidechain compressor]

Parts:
C23, C24: 100u; CP_Elec_6.3x7.7; LCSC C2836442
D6, D7: 1N5817; D_SOD-323; LCSC C5190152
J3: Conn_02x05_Odd_Even; IDC-Header_2x05_P2.54mm_Horizontal; Mouser Part no. 571-5103310-1
J4: Conn_01x02; PinHeader_1x02_P2.54mm_Vertical; Mouser Part no. 200-HTSW10207TS
J5: Conn_02x03_Odd_Even; PinHeader_2x03_P2.54mm_Vertical; Mouser Part no. 200-TSW10307TD

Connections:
-12V: C24.2, D7.2 (A), J5.5; also elsewhere on the board
unnamed: D6.2 (A), J3.9, J3.10
unnamed: D7.1 (K), J3.1, J3.2

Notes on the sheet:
UI power connection
Eurorack PSU connection

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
